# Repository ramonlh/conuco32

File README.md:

# DESARROLLO PARADO conuco32
¡¡¡DESARROLLO PARADO!!!
Conuco for ESP32
Hasta esta versión la comunicación entre principal y remotos se hacía con JSON. En la siguiente versión la comunicación se hace con MQTT.

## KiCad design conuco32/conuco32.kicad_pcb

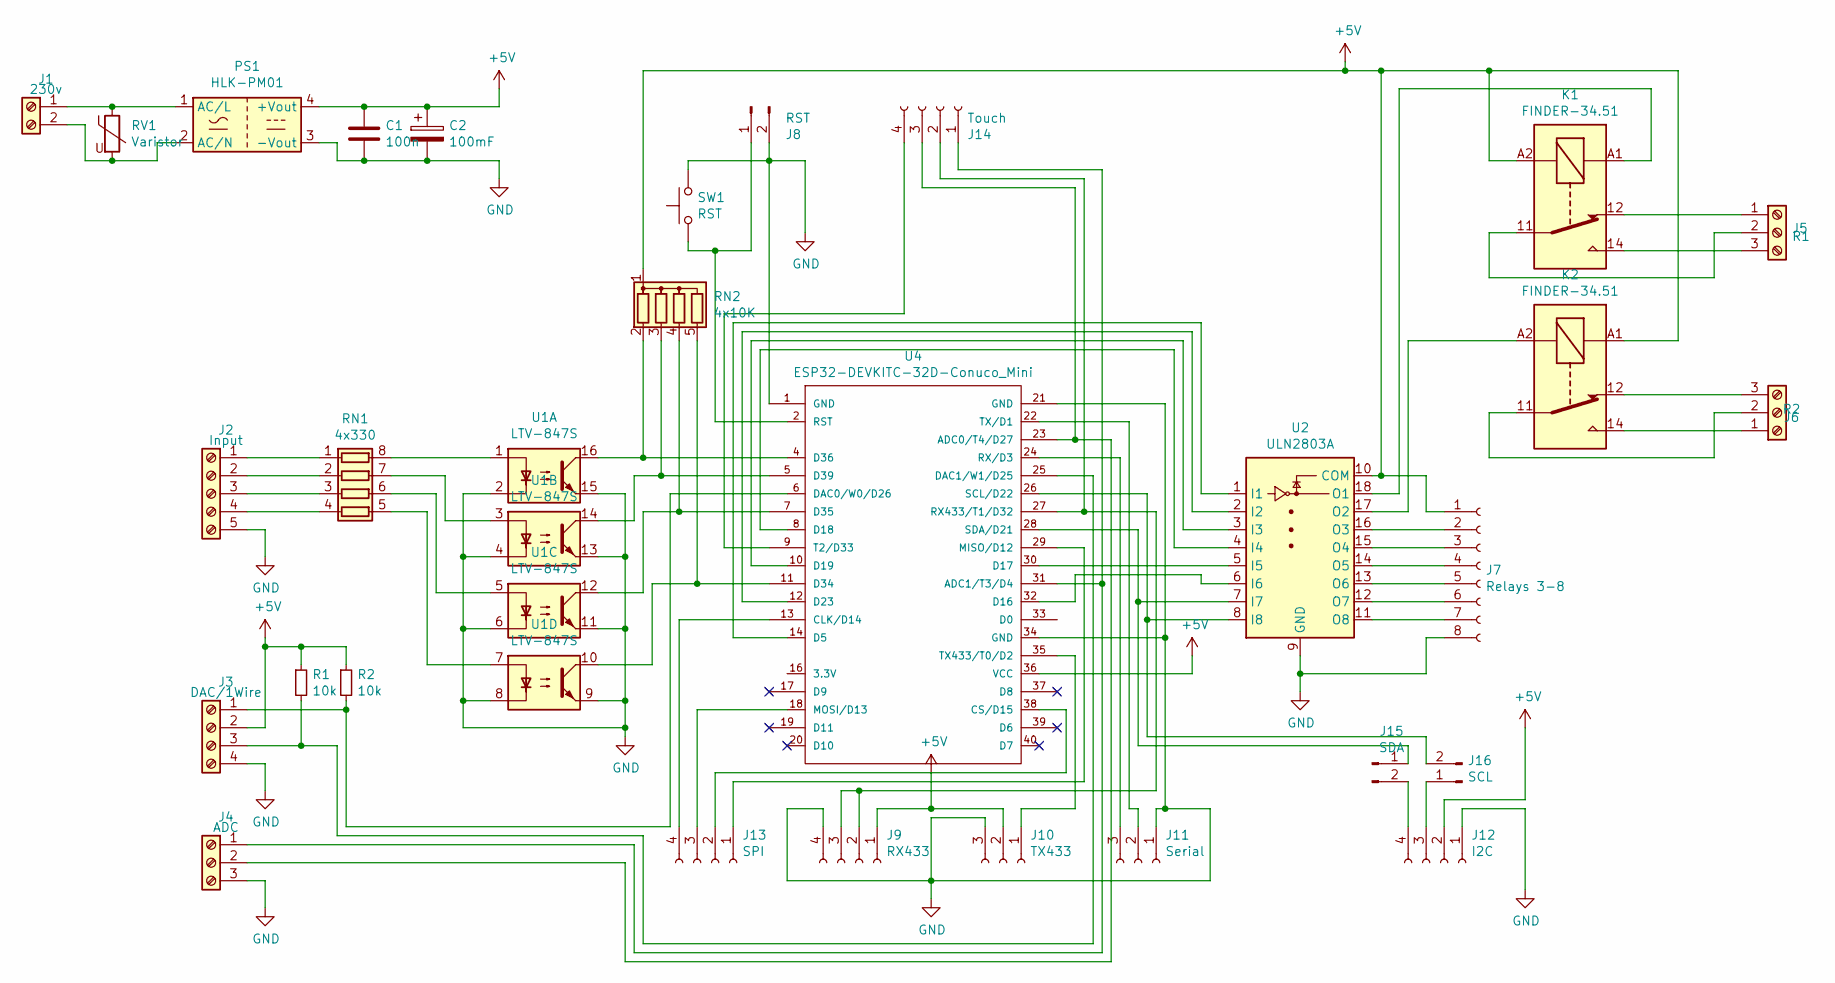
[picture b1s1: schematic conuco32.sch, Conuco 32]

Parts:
C1: 100n; C_Disc_D3.0mm_W2.0mm_P2.50mm
C2: 100mF; CP_Radial_D5.0mm_P2.50mm
J1: 230v; TerminalBlock_bornier-2_P5.08mm
J2: Input; TerminalBlock_bornier-5_P5.08mm
J3: DAC/1Wire; TerminalBlock_bornier-4_P5.08mm
J4: ADC; TerminalBlock_bornier-3_P5.08mm
J5: R1; TerminalBlock_bornier-3_P5.08mm
J6: R2; TerminalBlock_bornier-3_P5.08mm
J7: Relays 3-8; PinSocket_1x08_P2.54mm_Vertical
J8: RST; PinHeader_1x02_P2.54mm_Vertical
J9: RX433; PinSocket_1x04_P2.54mm_Vertical
J10: TX433; PinSocket_1x03_P2.54mm_Vertical
J11: Serial; PinSocket_1x03_P2.54mm_Vertical
J12: I2C; PinSocket_1x04_P2.54mm_Vertical
J13: SPI; PinSocket_1x04_P2.54mm_Vertical
J14: Touch; PinSocket_1x04_P2.54mm_Vertical
J15: SDA; PinHeader_1x02_P2.54mm_Vertical
J16: SCL; PinHeader_1x02_P2.54mm_Vertical
K1, K2: FINDER-34.51; Relay_SPDT_Finder_34.51_Vertical
PS1: HLK-PM01; Converter_ACDC_HiLink_HLK-PMxx
R1, R2: 10k; R_Axial_DIN0204_L3.6mm_D1.6mm_P1.90mm_Vertical
RN1: 4x330; SIP-8_19x3mm_P2.54mm
RN2: 4x10K; R_Array_SIP5
RV1: Varistor; RV_Disc_D9mm_W3.3mm_P5mm
SW1: RST; SW_PUSH_6mm_H8mm
U1: LTV-847S; SMDIP-16_W9.53mm
U2: ULN2803A; SOP-18_7.0x12.5mm_P1.27mm
U4: ESP32-DEVKITC-32D-Conuco_Mini; MODULE_ESP32-DEVKIT-32D-ConucoMini

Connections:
GND: C1.2, C2.2, J2.5, J3.4, J4.3, J7.8, J8.2, J9.4, J10.3, J11.1, J12.1, PS1.3 (-Vout), SW1.2, U1.2, U1.4, U1.6, U1.8, U1.9, U1.11, U1.13, U1.15, U2.9 (GND), U4.1 (GND), U4.21 (GND), U4.34 (GND)
unnamed: J1.1, PS1.1 (AC/L), RV1.1
unnamed: J1.2, PS1.2 (AC/N), RV1.2
unnamed: J2.1, RN1.1 (R1.1)
unnamed: J2.2, RN1.2 (R2.1)
unnamed: J2.3, RN1.3 (R3.1)
unnamed: J2.4, RN1.4 (R4.1)
unnamed: J3.1, R2.2, U4.6 (DAC0/W0/D26)
unnamed: J3.3, R1.2, U4.25 (DAC1/W1/D25)
unnamed: J5.1, K1.12
unnamed: J5.2, K1.11
unnamed: J5.3, K1.14
unnamed: J6.1, K2.14
unnamed: J6.2, K2.11
unnamed: J6.3, K2.12
unnamed: J7.2, U2.16 (O3)
unnamed: J7.3, U2.15 (O4)
unnamed: J7.4, U2.14 (O5)
unnamed: J7.5, U2.13 (O6)
unnamed: J7.6, U2.12 (O7)
unnamed: J7.7, U2.11 (O8)
unnamed: J8.1, SW1.1, U4.2 (RST)
unnamed: J10.1, U4.35 (TX433/T0/D2)
unnamed: J11.2, U4.22 (TX/D1)
unnamed: J11.3, U4.24 (RX/D3)
unnamed: J12.3, J16.1
unnamed: J12.4, J15.2
unnamed: J13.1, U4.29 (MISO/D12)
unnamed: J13.3, U4.18 (MOSI/D13)
unnamed: J13.4, U4.13 (CLK/D14)
unnamed: J4.1, J14.1, U4.31 (ADC1/T3/D4)
unnamed: J9.2, J9.3, J14.2, U4.27 (RX433/T1/D32)
unnamed: J4.2, J14.3, U4.23 (ADC0/T4/D27)
unnamed: J14.4, U4.9 (T2/D33)
unnamed: J15.1, U2.7 (I7), U4.28 (SDA/D21)
unnamed: J16.2, U2.8 (I8), U4.26 (SCL/D22)
unnamed: K1.A1, U2.18 (O1)
unnamed: K2.A2, U2.17 (O2)
unnamed: RN1.5 (R4.2), U1.7
unnamed: RN1.6 (R3.2), U1.5
unnamed: RN1.7 (R2.2), U1.3
unnamed: RN1.8 (R1.2), U1.1
unnamed: RN2.2 (R1), U1.16, U4.4 (D36)
unnamed: RN2.3 (R2), U1.14, U4.5 (D39)
unnamed: RN2.4 (R3), U1.12, U4.7 (D35)
unnamed: RN2.5 (R4), U1.10, U4.11 (D34)
unnamed: U2.1 (I1), U4.14 (D5)
unnamed: U2.2 (I2), U4.12 (D23)
unnamed: U2.3 (I3), U4.10 (D19)
unnamed: U2.4 (I4), U4.8 (D18)
unnamed: U2.5 (I5), U4.30 (D17)
unnamed: U2.6 (I6), U4.32 (D16)

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
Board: 2 copper layers, 30 parts (0 on the bottom side), 54 nets, no tracks yet.

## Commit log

2019-03-08 Versión inicial de conuco para ESP32
2020-02-09 Se añade gestión básica de sondas DS18B20
    Se añade gestión básica de sondas DS18B20: puede asignarse cada sonda en concreto a cada una de las posiciones 1 a 8.
2020-03-09 Versión con setup vía TFT
    Versión con configuración básica de WiFi vía TFT táctil
2020-07-25 Corrección errores
